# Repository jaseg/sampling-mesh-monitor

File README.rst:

High Fidelity Security Mesh Monitoring using Low-Cost, Embedded Time Domain Reflectometry
=========================================================================================

This repository contains all sources for our paper "High Fidelity Security Mesh Monitoring using Low-Cost, Embedded Time
Domain Reflectometry" to be published in CHES 2026/1 (`preprint on eprint <https://eprint.iacr.org/2025/1962>`__). You
can find a brief overview of the project `on Jan's blog <https://jaseg.de/blog/paper-sampling-mesh-monitor/>`__.

The canonical hosting location for this repo is https://git.jaseg.de/sampling-mesh-monitor.git . For comments or
questions, please reach out to Jan via `email <mailto:research@jaseg.de>`__ or `on mastodon
<https://chaos.social/@jaseg>`__.

.. figure:: paper/pic_board_setup_2_small.jpg
    :align: center
    :width: 400px
    :alt: A PCB with several chips sitting on a table with another PCB with only traces on it plugged in through a
          board-edge connector. The first PCB looks not very complex.

    The final setup. On the right is the measurement board, and on the left is the mesh test specimen plugged in. In a
    real application, you would integrate both into your target circuit.

Paper abstract
--------------

    Security Meshes are patterns of sensing traces covering an area that are used in Hardware Security Modules (HSMs)
    and other systems to detect attempts to physically intrude into the device's protective shell. State-of-the-art
    solutions manufacture meshes in bespoke processes from carefully chosen materials, which is expensive and makes
    replication challenging. Additionally, state-of-the-art monitoring circuits sacrifice either monitoring precision or
    cost efficiency. In this paper, we present an embeddable security mesh monitoring circuit constructed from low-cost,
    standard components that utilizes Time Domain Reflectometry (TDR) to create a unique fingerprint of a mesh. Our
    approach is both low-cost and precise, and enables the use of inexpensive standard Printed Circuit Boards (PCBs) as
    security mesh material. We demonstrate a working prototype of our TDR circuit costing less than 10 € in components
    that achieves both time resolution and rise time better than 200 ps—a 25 × improvement over previous work. We
    demonstrate a simple classifier that detects several types of advanced attacks such as probing using an oscilloscope
    probe or micro-soldering attacks with no false negatives.

Repo structure
--------------

``main_pcb``
    KiCad design files, exports and manufacturing files for the main circuit board. This board contains the measurement
    circuit, and has a connector for test coupons to be inserted. Data is read out throught the SWD interface using an
    SWD adapter. The board is a 6-layer PCB. The circuit is described in detail in the paper. It is based around a
    ``STM32G474RE`` ARM microcontroller.

``test_coupons``
    KiCad design files, exports and manufacturing files for the test coupon PCBs. The coupons are four-layer boards.
    Each coupon contains four test meshes, two on each side, that can be connected through four SFP form factor board
    edge connectors at the coupon's corners.

``firmware``
    Source code for the board firmware as well as tooling for running the experiments. The firmware is written in C, and
    you'll need a standard ARM GCC/binutils toolchain to build it. The experiment tool is a python script that connects
    to the board through GDB and exposes a local web server for controlling the board, monitoring the measurements in
    real time, and capturing data.

``analysis``
    All raw data, as well as the Jupyter notebooks used for analysis and plotting. By running these notebooks, you can
    re-run the analysis, and re-export all plots in the paper. The raw data is contained in JSON files, one per
    measurement series. Each JSON file contains some metadata describing the experiment and the settings used during the
    experiment, a set of calibration runs with the target specimen disconnected using the board's routing switches, and
    a full set of 12 measurement arrays consisting of a mean and standard deviation for each data point. To save space,
    batches of these JSON files are aggregated into zip archives. The analysis Jupyter notebooks will automatically load
    and decode the data from these zip archives when run.

``paper``
    The source of the accepted TCHES 2026-01 paper, as well as exports of all plots.

``talk``
    The presentation slides of the talk at CHES 2026 in Antalya, Türkiye.

Running the analysis
--------------------

To re-run the analysis, first install `Jupyter Lab <https://jupyter.org/>`__ and the `numpy <https://numpy.org/>`__ and
`scipy <https://scipy.org/>`__ python packages. If you're running in a virtualenv or on a weird platform like Windows or
MacOS, make sure that jupyter and pip agree where your python lives and the packages get installed in the right place.

Afterwards, just run ``jupyter lab`` in the ``analysis/jupyter_notebooks`` directory. You can then open any of the
notebooks through the left side panel and re-run the analysis within. Make sure you run all of the setup code at the top
of the notebook once before trying to run the analaysis code in the cells below. The analysis code only uses standard
scientific python packages that you probably already have installed. If you get an ``ImportError``, make sure the
packages listed in the file ``analysis/jupyter_notebooks/requirements.txt`` are installed.

The notebooks will display the plots and results inside Jupyter Lab and will also automatically export the plots to the
``paper`` directory of your clone of the git repository.

PCB Designs
-----------

This repo includes both the raw CAD files of the PCBs, as well as exported manufacturing data for easier viewing if you
don't have KiCad installed. The schematics are included as PDF exports.

The PCB designs were prepared in the open source KiCad_ EDA tool. Note that for some files you might need to download a
KiCad nightly build depending on how new your KiCad version is.

PCB design folder structure
...........................

``foobar.{kicad_pro,kicad_sch,kicad_pcb,etc.}``
    The KiCad source files of the PCB. Open the ``.kicad_pro`` file in KiCad, then you can open the schematics and board
    layout from there.

``fab/gerbers.zip``
    Gerber exports of the board layouts. You can open these in any Gerber viewer such as gerbv_. These files are
    essentially vector graphics exports of the board layout. They show what copper, silkscreen etc. you see on the
    board, but they don't include any semantic information such as component values. You can send this zip directly to a
    PCB manufacturer and they will be able to manufacture these boards for you. The order parameters are included in the
    gerber files on the ``User.Comments`` layer.

``fab/{bom.csv,pos.csv}``
    Bill of materials and component placement coordinate files for board manufacturing. If you want a contract
    manufacturer to solder these boards for you, you need to give them these two files in addition to the gerbers. The
    BOM tells them what exact parts and how many of them you need, the position file tells them where to put them on the
    board. We had JLCPCB make the PCBs, and we also had them solder most of the parts. Some parts we soldered after the
    fact by hand because JLC didn't have them in stock, and getting them to order and solder them for us would have been
    pretty expensive.

    If you want to solder the main PCB yourself, you need some prior experience in fine SMD work and a decently setup
    electronics lab with a microscope, a hot air reworks station, etc.

    Note: **The PCB revision here does not have a functional driver IC!** For our lab experiments we microsoldered
    the four different driver ICs by hand to avoid having to spin multiple copies of this expensive PCB. For some basic
    measurements, you can just omit the driver IC included in the design and bridge it. This will drive the mesh
    directly from the ``74LVC2G157`` gates, which is enough for some basic measurements.

``schematics/*.pdf``
    PDF export of the schematics of the board.

Firmware
--------

The firmware and associated scripts are contained in the ``firmware`` directory.

Building the firmware
.....................

If you have an ARM GCC toolchain installed, you can build the firmware by running ``make`` in this directory. During
build, the makefile exports some diagnostic information about the build artifacts. For that to work, you have to have
the `cxxfilt python package <https://pypi.org/project/cxxfilt/>`__ installed. If the package can't be found, the
firmware will still be built, but you will get a crash in the makefile during the analysis step that runs after the
build was successful.

Running experiments
...................

To run an experiment, you need a measurement board and a test coupon. You also need the following software installed on
your machine:

* ``openocd``
* ``arm-none-eabi-gdb`` (another ABI arm gdb should work too)
* The python packages listed in ``firmware/requirements.txt``

To build the firmware, you additionally need a ARM toolchain installed. By default, the makefile assumes gcc/gnu
binutils, but you can override that if you prefer to use LLVM.

To run an experiment, connect the board to power via USB, and to your computer through an SWD debug adapter. We used
cheap STLinkV2 clones, if you have a different adapter you'll have to modify the ``.gdbinit`` script accordingly. After
connecting the board, open three terminal windows running the following three commands one per window, in this order.

1. ``openocd -f openocd.cfg``
2. ``arm-none-eabi-gdb build/main.elf``
3. ``python adc_serve.py``

This will connect to the board and start the realtime control and measurement web interface. You can open the web
interface at the location printed by ``adc_serve.py`` on startup.

If you're cheap like us and use a STLinkV2 clone SWD adapter, it may be that openocd takes a few (maybe up to five or
so) attempts to start up and connect to the microcontroller. After starting, the GDB terminal should start printing a
few lines of output every 30 seconds or so when it saves a measurement series. If GDB starts to hang, it might be that
you bumped a cable or accidentially shorted something on the board. To re-start, you first kill gdb (Ctrl+C, then
Ctrl+D, then Ctrl+D again), then you stop openocd (Ctrl+C, kill it if it doesn't stop in a few seconds), then you
restart them in the order above. You don't have to restart the web interface, just adjust any of the knobs to overwrite
the default control settings again.

Firmware Folder Structure
.........................

``src/main.c``
    The source code of the mainboard firmware. This firmware captures data into internal buffers, which are read out
    from the host through SWD.

``openocd.cfg``
    OpenOCD script for connecting to the debug adapter. We used cheap STLinkV2 clones from aliexpress. If you use a
    different debug adapter, you will have to modify this file accordingly to tell OpenOCD how to connect to the board.
    The port numbers given here and in the ``.gdbinit`` must match up.

``.gdbinit``
    GDB script running the data extraction. This script will continuously dump the measurement data into ``/tmp`` every
    time a measurement series has been completed. Note that this file will be hidden on unixes. Also note that you will
    have to explicitly allowlist this file's absolute path on your computer in your ``$HOME/.gdbinit`` the first time
    you run it because gdb refuses to run unknown ``.gdbinit`` files for security.

``adc_serve.py``
    Real-time monitoring and data capture tool. Before running this, first make sure you have gdb attached to the board
    using the ``.gdbinit``. The tool communicates with the gdb script through files in ``/tmp``. It exposes a web
    interface that displays the captured data in real time, allows you to change the board's measurement settings, and
    allows you to export measurement series.

``make_barcodes.py``
    This is a helper script we used to create barcode labels for all ~120 test specimens to simplify the measurement
    workflow. We had a barcode reader hooked up to the computer running the measurements, so you could just scan a
    specimen's barcode to capture a data series registered to that board in the web interface.
    
other files:
    Build files for the firmware. These are mostly generic to this type of microcontroller and are included here so the
    firmware source is self-contained.

.. _KiCad: https://www.kicad.org/
.. _gerbv: https://gerbv.github.io/

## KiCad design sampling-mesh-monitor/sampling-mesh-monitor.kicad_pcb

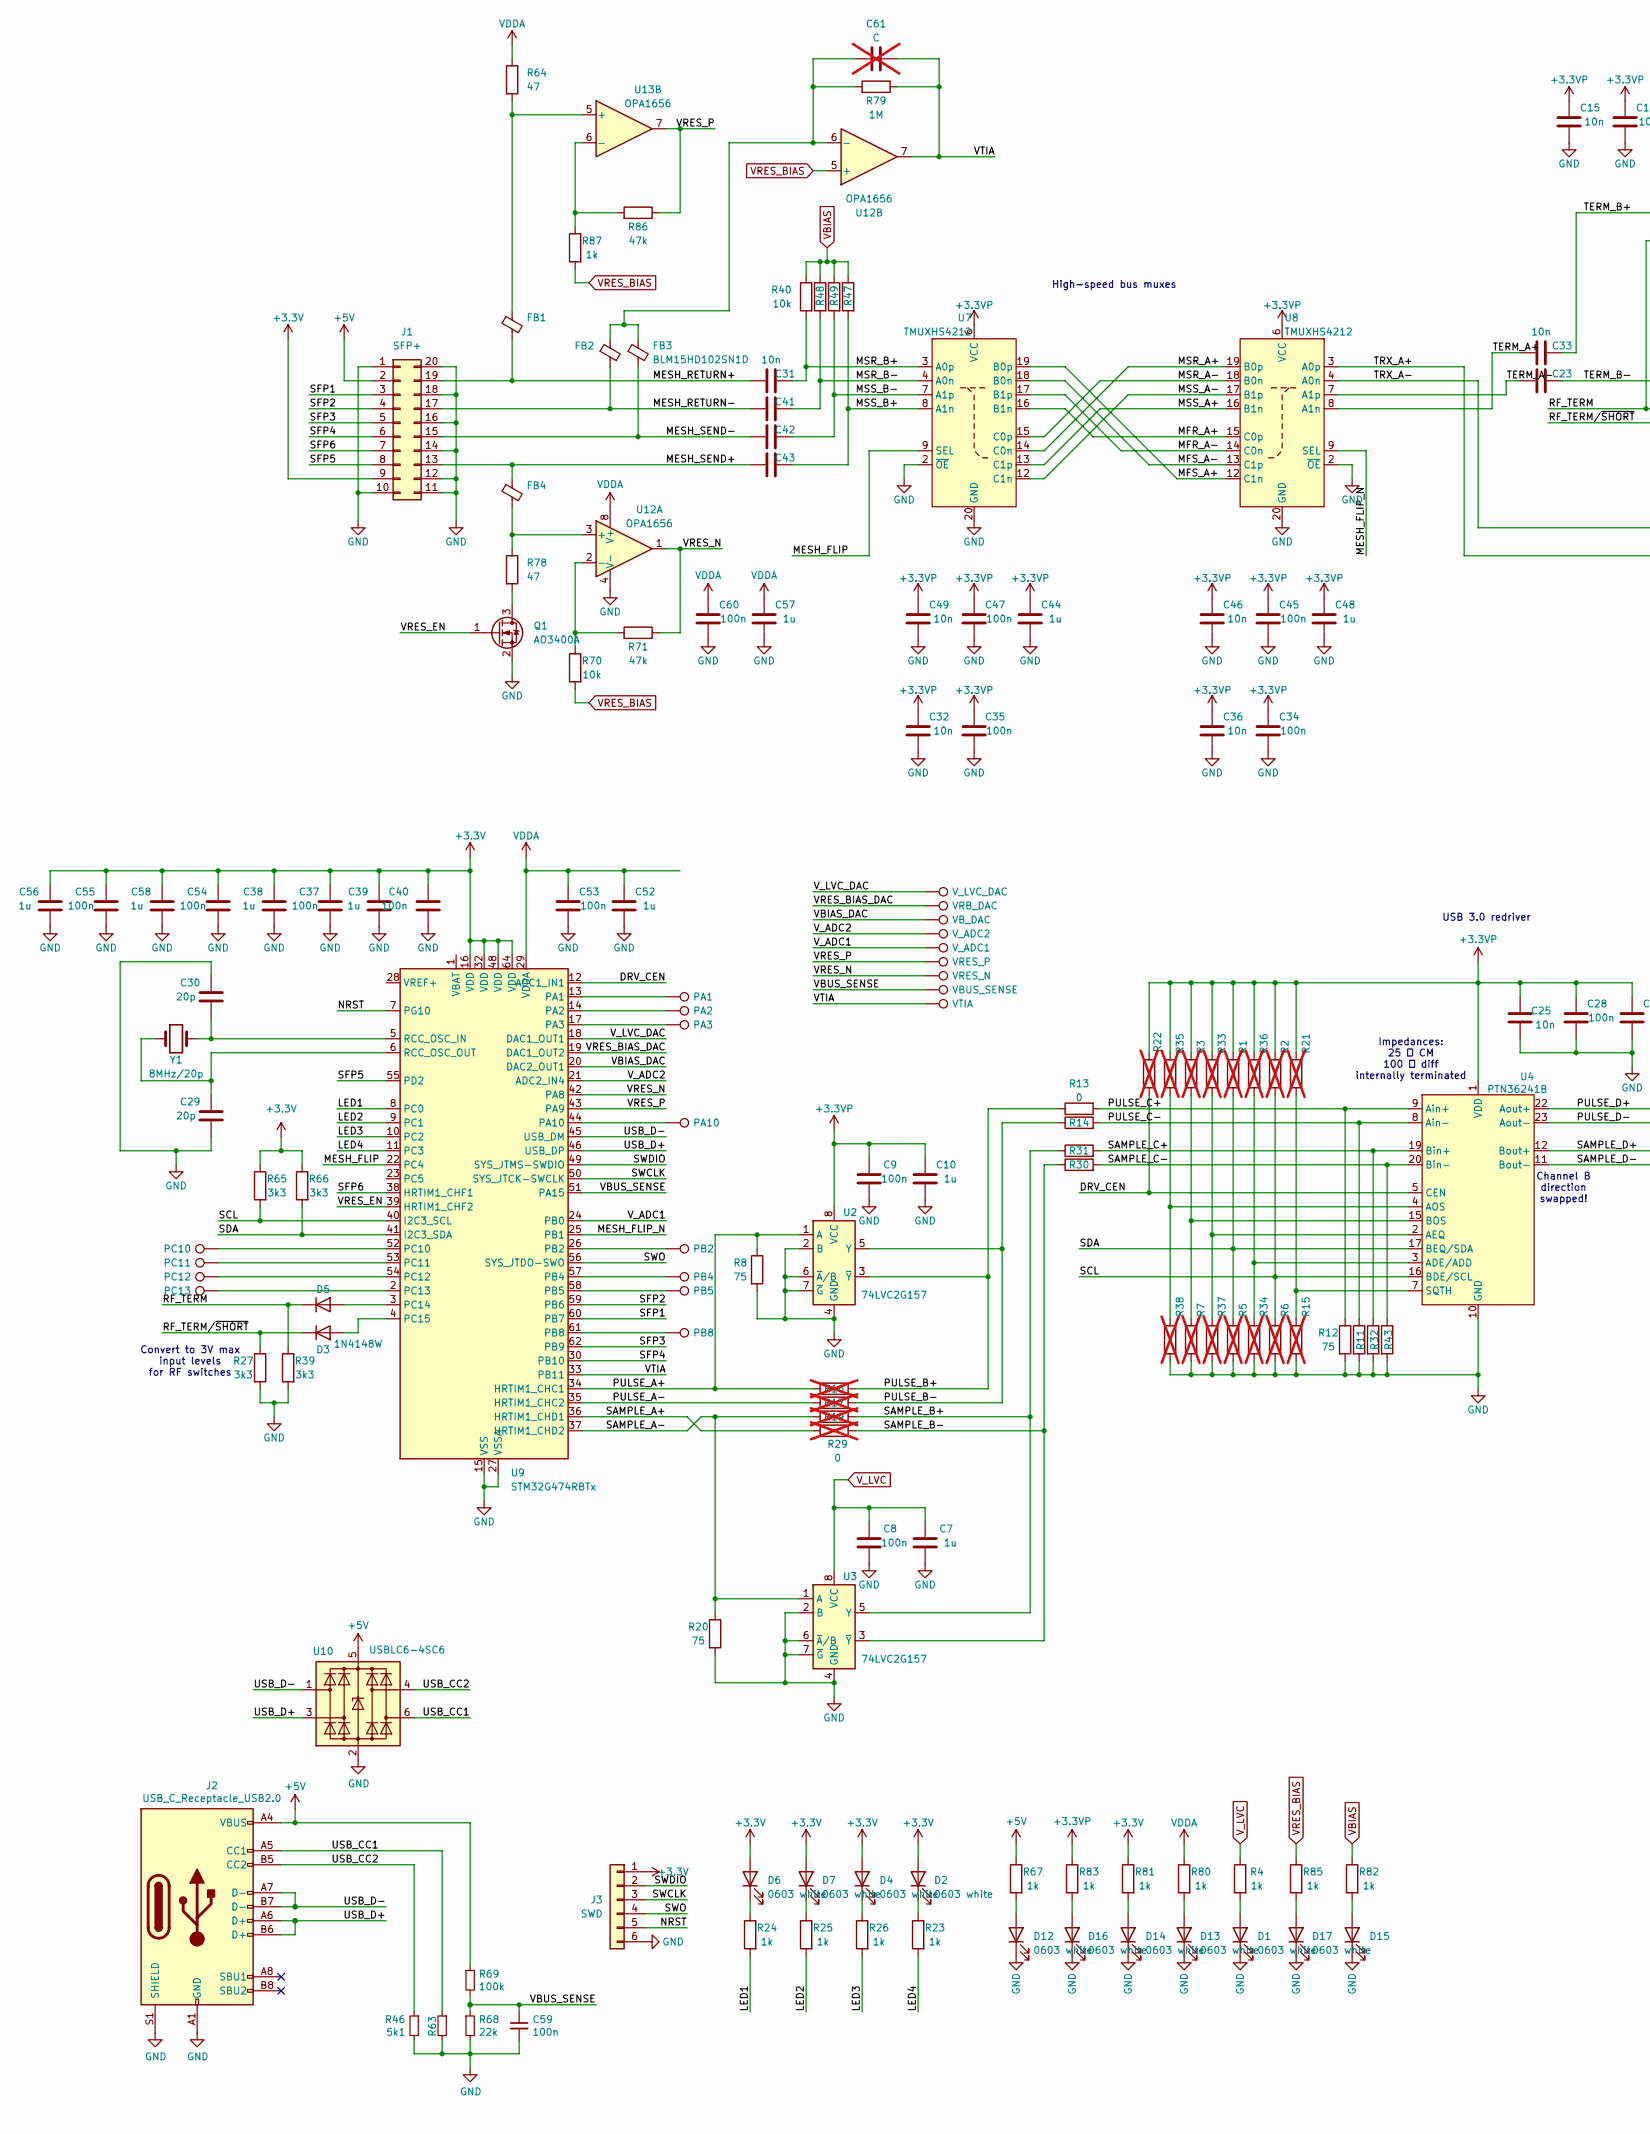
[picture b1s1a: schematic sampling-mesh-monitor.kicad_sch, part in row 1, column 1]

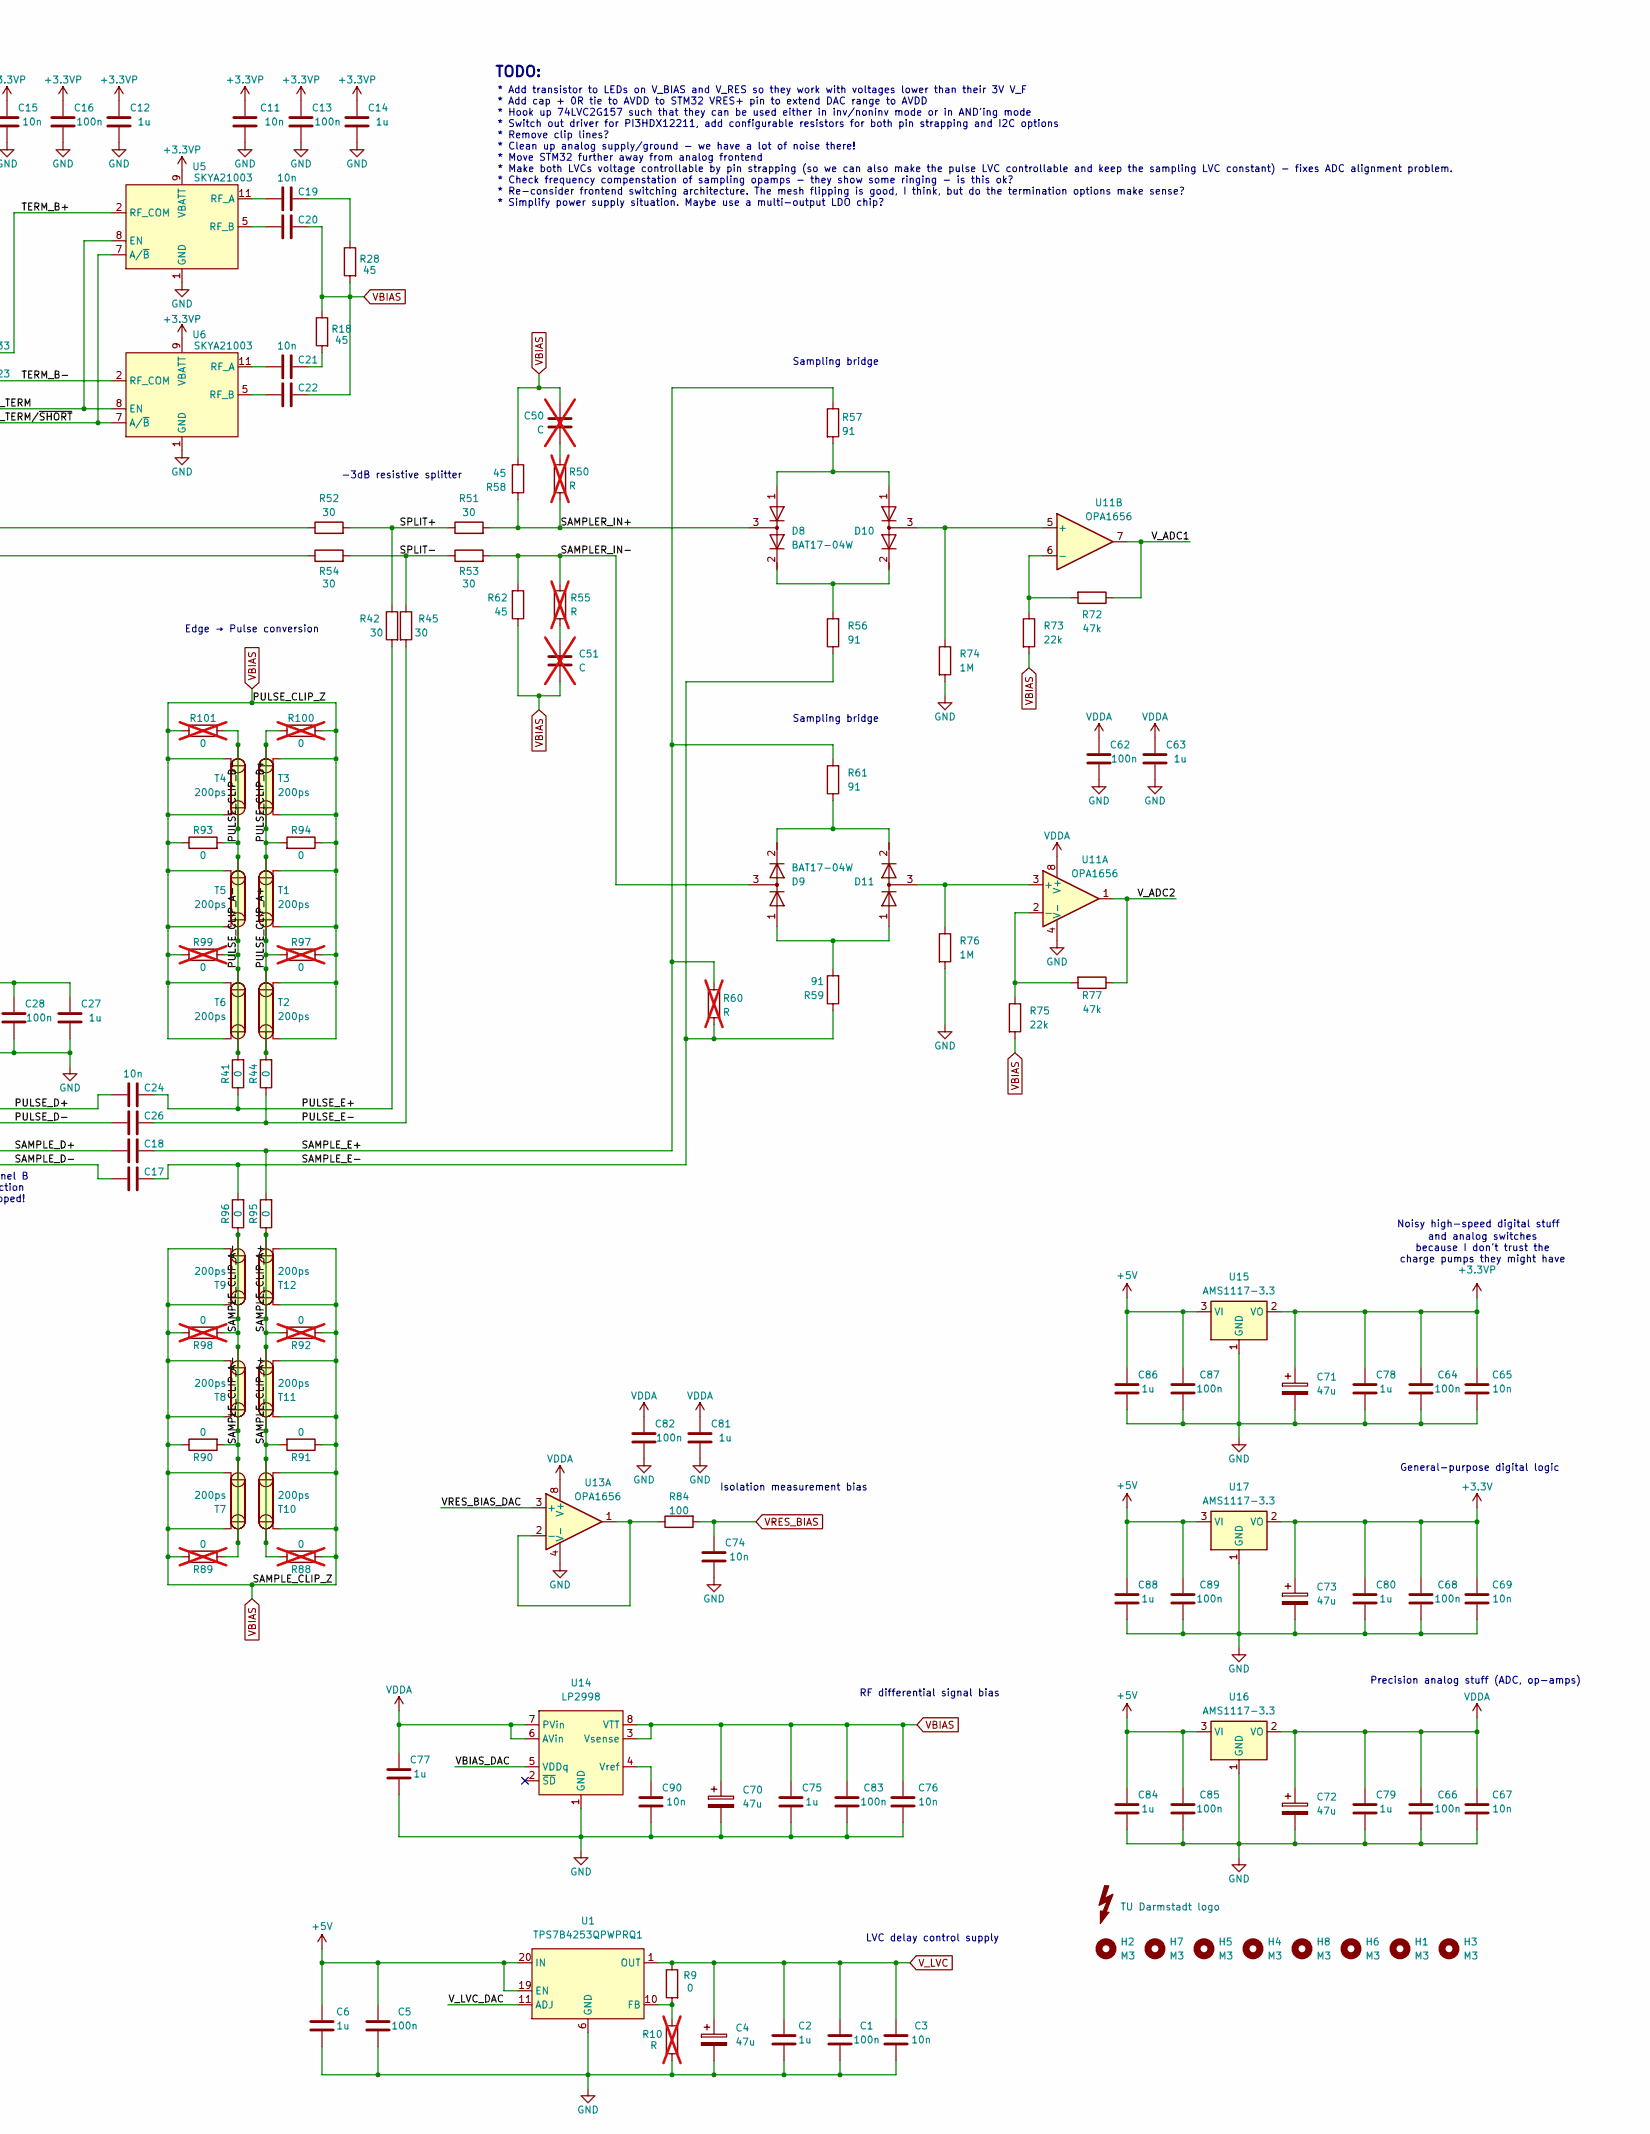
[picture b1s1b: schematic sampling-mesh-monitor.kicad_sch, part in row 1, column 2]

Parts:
C1, C5, C8, C9, C13, C16, C28, C34, C35, C37, C40, C45, C47, C53, C54, C55, C59, C60, C62, C64, C66, C68, C82, C83, C85, C87, C89: 100n; C_0402_1005Metric; LCSC C307331
C2, C6, C7, C10, C12, C14, C27, C38, C39, C44, C48, C52, C56, C57, C58, C63, C75, C77, C78, C79, C80, C81, C84, C86, C88: 1u; C_0805_2012Metric; LCSC C28323
C3, C11, C15, C17, C18, C19, C20, C21, C22, C23, C24, C25, C26, C31, C32, C33, C36, C41, C42, C43, C46, C49, C65, C67, C69, C74, C76, C90: 10n; C_0402_1005Metric; LCSC C15195
C4, C70, C71, C72, C73: 47u; C_Elec_6.3x7.7; LCSC C88810
C29, C30: 20p; C_0402_1005Metric; LCSC C1554
C50, C51, C61: C; C_0402_1005Metric; not fitted
D1, D2, D4, D6, D7, D12, D13, D14, D15, D16, D17: 0603 white; LED_0603_1608Metric; LCSC C2290
D3, D5: 1N4148W; D_SOD-123; LCSC C81598
D8, D9, D10, D11: BAT17-04W; SOT-323_SC-70; LCSC C503474
FB1, FB2, FB3, FB4: BLM15HD102SN1D; L_0402_1005Metric; LCSC C21516
GR1: TU Darmstadt logo; logo_tu_darmstadt_25.0mm
H1, H2, H3, H4, H5, H6, H7, H8: M3; MountingHole_3.2mm_M3_DIN965
J1: SFP+; HCTL_HC-SFP-20P_C2897291; LCSC C2897291
J2: USB_C_Receptacle_USB2.0; USB_C_Receptacle_HCTL_HC-TYPE-C-16P-01A; LCSC C2988369
J3: SWD; Würth_WR-WST_debug_490107670612_2x03_P2.54mm_Vertical
Q1: AO3400A; SOT-23; LCSC C20917
R1, R2, R3, R5, R6, R7, R10, R15, R21, R22, R33, R34, R35, R36, R37, R38, R50, R55, R60: R; R_0402_1005Metric; not fitted
R4, R23, R24, R25, R26, R67, R80, R81, R82, R83, R85, R87: 1k; R_0402_1005Metric; LCSC C11702
R8, R11, R12, R20, R32, R43: 75; R_0402_1005Metric; LCSC C25133
R9, R13, R14, R30, R31, R41, R44, R90, R91, R93, R94, R95, R96: 0; R_0402_1005Metric; LCSC C17168
R16, R17, R19, R29, R88, R89, R92, R97, R98, R99, R100, R101: 0; R_0402_1005Metric; LCSC C17168; not fitted
R18, R28, R58, R62: 45; R_0402_1005Metric; LCSC C327342
R27, R39, R65, R66: 3k3; R_0402_1005Metric; LCSC C25890
R40, R47, R48, R49, R70: 10k; R_0402_1005Metric; LCSC C2654005
R42, R45, R51, R52, R53, R54: 30; R_0402_1005Metric; LCSC C138007
R46, R63: 5k1; R_0402_1005Metric; LCSC C25905
R56, R57, R59, R61: 91; R_0402_1005Metric; LCSC C4071412
R64, R78: 47; R_0603_1608Metric; LCSC C23182
R68, R73, R75: 22k; R_0402_1005Metric; LCSC C25768
R69: 100k; R_0402_1005Metric; LCSC C25741
R71, R72, R77, R86: 47k; R_0402_1005Metric; LCSC C25792
R74, R76, R79: 1M; R_0402_1005Metric; LCSC C138033
R84: 100; R_0402_1005Metric; LCSC C25076
T1, T2, T3, T4, T5, T6, T7, T8, T9, T10, T11, T12: 200ps
TP1: V_LVC_DAC; TestPoint_Pad_1.5x1.5mm
TP2: PA2; TestPoint_Pad_1.5x1.5mm
TP3: PA1; TestPoint_Pad_1.5x1.5mm
TP4: PC13; TestPoint_Pad_1.5x1.5mm
TP5: VRB_DAC; TestPoint_Pad_1.5x1.5mm
TP6: PA3; TestPoint_Pad_1.5x1.5mm
TP7: PB2; TestPoint_Pad_1.5x1.5mm
TP8: PB5; TestPoint_Pad_1.5x1.5mm
TP9: PB8; TestPoint_Pad_1.5x1.5mm
TP10: PC12; TestPoint_Pad_1.5x1.5mm
TP11: PB4; TestPoint_Pad_1.5x1.5mm
TP12: PC11; TestPoint_Pad_1.5x1.5mm
TP13: PC10; TestPoint_Pad_1.5x1.5mm
TP14: PA10; TestPoint_Pad_1.5x1.5mm
TP15: VBUS_SENSE; TestPoint_Pad_1.5x1.5mm
TP16: VRES_N; TestPoint_Pad_1.5x1.5mm
TP17: VTIA; TestPoint_Pad_1.5x1.5mm
TP18: V_ADC1; TestPoint_Pad_1.5x1.5mm
TP19: V_ADC2; TestPoint_Pad_1.5x1.5mm
TP20: VRES_P; TestPoint_Pad_1.5x1.5mm
TP21: VB_DAC; TestPoint_Pad_1.5x1.5mm
U1: TPS7B4253QPWPRQ1; HTSSOP-20-1EP_4.4x6.5mm_P0.65mm_EP3.4x6.5mm_Mask2.4x3.7mm; LCSC C2879376
U2, U3: 74LVC2G157; MSOP-8_3x3mm_P0.65mm; LCSC C78048
U4: PTN36241B; QFN-24-1EP_4x4mm_P0.5mm_EP2.6x2.6mm; LCSC C2675242
U5, U6: SKYA21003; QFN-12_EP_2x2_Pitch0.5mm; LCSC C141440
U7, U8: TMUXHS4212; DHVQFN-20-1EP_2.5x4.5mm_P0.5mm_EP1x3mm; LCSC C3656912
U9: STM32G474RBTx; LQFP-64_10x10mm_P0.5mm; LCSC C529413
U10: USBLC6-4SC6; SOT-23-6; LCSC C558419
U11, U12, U13: OPA1656; SO-8_3.9x4.9mm_P1.27mm; LCSC C1849431
U14: LP2998; SOIC-8-1EP_3.9x4.9mm_P1.27mm_EP2.34x2.34mm; LCSC C181400
U15, U16, U17: AMS1117-3.3; SOT-223-3_TabPin2; LCSC C6186
Y1: 8MHz/20p; Crystal_SMD_5032-2Pin_5.0x3.2mm; LCSC C115962

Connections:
+3.3V: C37.2, C38.2, C39.2, C40.2, C54.2, C55.2, C56.2, C58.2, C68.2, C69.2, C73.1, C80.2, D2.2 (A), D4.2 (A), D6.2 (A), D7.2 (A), J1.9, J3.1, R65.1, R66.1, R81.1, U9.16 (VDD), U9.32 (VDD), U9.48 (VDD), U9.64 (VDD), U17.2 (VO)
+3.3VP: C9.2, C10.2, C11.2, C12.2, C13.2, C14.2, C15.2, C16.2, C25.2, C27.2, C28.2, C32.2, C34.2, C35.2, C36.2, C44.2, C45.2, C46.2, C47.2, C48.2, C49.2, C64.2, C65.2, C71.1, C78.2, R1.1, R2.1, R3.1, R21.1, R22.1, R33.1, R35.1, R36.1, R83.1, U2.8 (VCC), U4.1 (VDD), U4.13 (VDD), U5.9 (VBATT), U6.9 (VBATT), U7.1 (RSVD1), U7.6 (VCC), U7.10 (RSVD2), U8.1 (RSVD1), U8.6 (VCC), U8.10 (RSVD2), U15.2 (VO)
+5V: C5.2, C6.2, C84.2, C85.2, C86.2, C87.2, C88.2, C89.2, J1.2, J2.A4 (VBUS), J2.A9 (VBUS), J2.B4 (VBUS), J2.B9 (VBUS), R67.1, R69.1, U1.19 (EN), U1.20 (IN), U10.5 (VBUS), U15.3 (VI), U16.3 (VI), U17.3 (VI)
/DRV_CEN: R22.2, U4.5 (CEN), U9.12 (ADC1_IN1)
/LED1: R24.2, U9.8 (PC0)
/LED2: R25.2, U9.9 (PC1)
/LED3: R26.2, U9.10 (PC2)
/LED4: R23.2, U9.11 (PC3)
/MESH_FLIP: U7.9 (SEL), U9.22 (PC4)
/MESH_FLIP_N: U8.9 (SEL), U9.25 (PB1)
/MESH_RETURN+: C31.1, FB1.2, J1.19
/MESH_RETURN-: C41.1, FB2.2, J1.17
/MESH_SEND+: C43.1, FB4.1, J1.13
/MESH_SEND-: C42.1, FB3.2, J1.15
/MFR_A+: U7.16 (B1n), U8.15 (C0p)
/MFR_A-: U7.17 (B1p), U8.14 (C0n)
/MFS_A+: U7.19 (B0p), U8.12 (C1n)
/MFS_A-: U7.18 (B0n), U8.13 (C1p)
/MSR_A+: U7.14 (C0n), U8.19 (B0p)
/MSR_A-: U7.15 (C0p), U8.18 (B0n)
/MSR_B+: C31.2, R40.2, U7.3 (A0p)
/MSR_B-: C41.2, R48.2, U7.4 (A0n)
/MSS_A+: U7.13 (C1p), U8.16 (B1n)
/MSS_A-: U7.12 (C1n), U8.17 (B1p)
/MSS_B+: C43.2, R47.2, U7.8 (A1n)
/MSS_B-: C42.2, R49.2, U7.7 (A1p)
/NRST: J3.5, U9.7 (PG10)
/PULSE_A+: R8.1, R16.1, U2.1 (A), U9.34 (HRTIM1_CHC1)
/PULSE_A-: R17.1, U9.35 (HRTIM1_CHC2)
/PULSE_B+: R13.1, R16.2, U2.3 (~Y)
/PULSE_B-: R14.1, R17.2, U2.5 (Y)
/PULSE_C+: R12.1, R13.2, U4.9 (Ain+)
/PULSE_C-: R11.1, R14.2, U4.8 (Ain-)
/PULSE_CLIP_A+: R44.2, R94.2, R97.2, R100.2, T1.1, T1.3, T2.1, T2.3, T3.1, T3.3
/PULSE_CLIP_A-: R41.2, R93.2, R99.2, R101.2, T4.1, T4.3, T5.1, T5.3, T6.1, T6.3
/PULSE_D+: C24.2, U4.22 (Aout+)
/PULSE_D-: C26.2, U4.23 (Aout-)
/PULSE_E+: C24.1, R41.1, R42.2
/PULSE_E-: C26.1, R44.1, R45.2
/RF_TERM: D5.1 (K), R39.1, U5.8 (EN), U6.8 (EN)
/RF_TERM/~SHORT: D3.1 (K), R27.1, U5.7 (A/~B), U6.7 (A/~B)
/SAMPLER_IN+: D8.3 (common), R50.2, R51.2, R58.2
/SAMPLER_IN-: D9.3 (common), R53.2, R55.2, R62.2
/SAMPLE_A+: R29.1, U9.36 (HRTIM1_CHD1)
/SAMPLE_A-: R19.1, R20.1, U3.1 (A), U9.37 (HRTIM1_CHD2)
/SAMPLE_B+: R19.2, R31.1, U3.5 (Y)
/SAMPLE_B-: R29.2, R30.1, U3.3 (~Y)
/SAMPLE_C+: R31.2, R32.1, U4.19 (Bin+)
/SAMPLE_C-: R30.2, R43.1, U4.20 (Bin-)
/SAMPLE_CLIP_A+: R88.2, R91.2, R92.2, R95.1, T10.1, T10.3, T11.1, T11.3, T12.1, T12.3
/SAMPLE_CLIP_A-: R89.2, R90.2, R96.1, R98.2, T7.1, T7.3, T8.1, T8.3, T9.1, T9.3
/SAMPLE_D+: C18.2, U4.12 (Bout+)
/SAMPLE_D-: C17.2, U4.11 (Bout-)
/SAMPLE_E+: C18.1, R57.1, R60.1, R61.2, R95.2
/SAMPLE_E-: C17.1, R56.1, R59.1, R60.2, R96.2
/SCL: R2.2, R6.1, R65.2, U4.16 (BDE/SCL), U9.40 (I2C3_SCL)
/SDA: R1.2, R5.1, R66.2, U4.17 (BEQ/SDA), U9.41 (I2C3_SDA)
/SFP1: J1.3, U9.60 (PB7)
/SFP2: J1.4, U9.59 (PB6)
/SFP3: J1.5, U9.62 (PB9)
/SFP4: J1.6, U9.30 (PB10)
/SFP5: J1.8, U9.55 (PD2)
/SFP6: J1.7, U9.38 (HRTIM1_CHF1)
/SPLIT+: R42.1, R51.1, R52.2
/SPLIT-: R45.1, R53.1, R54.2
/SWCLK: J3.3, U9.50 (SYS_JTCK-SWCLK)
/SWDIO: J3.2, U9.49 (SYS_JTMS-SWDIO)
/SWO: J3.4, U9.56 (SYS_JTDO-SWO)
/TERM_A+: C33.2, U8.8 (A1n)
/TERM_A-: C23.2, U8.7 (A1p)
/TERM_B+: C33.1, U5.2 (RF_COM)
/TRX_A+: R54.1, U8.3 (A0p)
/TRX_A-: R52.1, U8.4 (A0n)
/USB_CC1: J2.A5 (CC1), R63.1, U10.6 (I/O4)
/USB_CC2: J2.B5 (CC2), R46.1, U10.4 (I/O3)
/USB_D+: J2.A6 (D+), J2.B6 (D+), U9.46 (USB_DP), U10.3 (I/O2)
/USB_D-: J2.A7 (D-), J2.B7 (D-), U9.45 (USB_DM), U10.1 (I/O1)
/VBIAS_DAC: TP21.1, U9.20 (DAC2_OUT1), U14.5 (VDDq)
/VBUS_SENSE: C59.1, R68.1, R69.2, TP15.1, U9.51 (PA15)
/VRES_BIAS_DAC: TP5.1, U9.19 (DAC1_OUT2), U13.3 (+)
/VRES_EN: Q1.1 (G), U9.39 (HRTIM1_CHF2)
/VRES_N: R71.1, TP16.1, U9.42 (PA8), U12.1
/VRES_P: R86.1, TP20.1, U9.43 (PA9), U13.7
/VTIA: C61.2, R79.1, TP17.1, U9.33 (PB11), U12.7
/V_ADC1: R72.1, TP18.1, U9.24 (PB0), U11.7
/V_ADC2: R77.1, TP19.1, U9.21 (ADC2_IN4), U11.1
/V_LVC_DAC: TP1.1, U1.11 (ADJ), U9.18 (DAC1_OUT1)
GND: C1.1, C2.1, C3.1, C4.2, C5.1, C6.1, C7.1, C8.1, C9.1, C10.1, C11.1, C12.1, C13.1, C14.1, C15.1, C16.1, C25.1, C27.1, C28.1, C29.1, C30.2, C32.1, C34.1, C35.1, C36.1, C37.1, C38.1, C39.1, C40.1, C44.1, C45.1, C46.1, C47.1, C48.1, C49.1, C52.1, C53.1, C54.1, C55.1, C56.1, C57.1, C58.1, C59.2, C60.1, C62.1, C63.1, C64.1, C65.1, C66.1, C67.1, C68.1, C69.1, C70.2, C71.2, C72.2, C73.2, C74.1, C75.1, C76.1, C77.1, C78.1, C79.1, C80.1, C81.1, C82.1, C83.1, C84.1, C85.1, C86.1, C87.1, C88.1, C89.1, C90.1, D1.1 (K), D12.1 (K), D13.1 (K), D14.1 (K), D15.1 (K), D16.1 (K), D17.1 (K), J1.1, J1.10, J1.11, J1.12, J1.14, J1.16, J1.18, J1.20, J2.A1 (GND), J2.A12 (GND), J2.B1 (GND), J2.B12 (GND), J2.S1 (SHIELD), J3.6, Q1.2 (S), R5.2, R6.2, R7.2, R8.2, R10.2, R11.2, R12.2, R15.2, R20.2, R27.2, R32.2, R34.2, R37.2, R38.2, R39.2, R43.2, R46.2, R63.2, R68.2, R74.2, R76.2, U1.6 (GND), U1.15 (GND), U1.21 (GND), U2.2 (B), U2.4 (GND), U2.6 (~A/B), U2.7 (~G), U3.2 (B), U3.4 (GND), U3.6 (~A/B), U3.7 (~G), U4.6 (GND), U4.10 (GND), U4.14 (RES), U4.18 (GND), U4.21 (GND), U4.25 (GND), U5.1 (GND), U5.3 (GND), U5.4 (GND), U5.6 (GND), U5.10 (GND), U5.12 (GND), U5.13 (GND), U6.1 (GND), U6.3 (GND), U6.4 (GND), U6.6 (GND), U6.10 (GND), U6.12 (GND), U6.13 (GND), U7.2 (~OE), U7.5 (GND), U7.11 (GND), U7.20 (GND), U7.21 (GND), U8.2 (~OE), U8.5 (GND), U8.11 (GND), U8.20 (GND), U8.21 (GND), U9.15 (VSS), U9.27 (VSSA), U9.31 (VSS), U9.47 (VSS), U9.63 (VSS), U10.2 (GND), U11.4 (V-), U12.4 (V-), U13.4 (V-), U14.1 (GND), U14.9 (GND), U15.1 (GND), U16.1 (GND), U17.1 (GND)
unnamed: C50.2, R50.1
unnamed: C19.1, R28.1
unnamed: C21.1, R18.2
unnamed: C51.1, R55.1
unnamed: D8.1 (A), D10.1 (A), R57.2
unnamed: D8.2 (K), D10.2 (K), R56.2
unnamed: D10.3 (common), R74.1, U11.5 (+)
unnamed: D9.1 (A), D11.1 (A), R59.2
unnamed: D9.2 (K), D11.2 (K), R61.1
unnamed: D11.3 (common), R76.1, U11.3 (+)
unnamed: D5.2 (A), U9.3 (PC14)
unnamed: D3.2 (A), U9.4 (PC15)
unnamed: D7.1 (K), R25.1
unnamed: D6.1 (K), R24.1
unnamed: D4.1 (K), R26.1
unnamed: D2.1 (K), R23.1
unnamed: D12.2 (A), R67.2
unnamed: D16.2 (A), R83.2
unnamed: D14.2 (A), R81.2
unnamed: D13.2 (A), R80.2
unnamed: D1.2 (A), R4.2
unnamed: D17.2 (A), R85.2
unnamed: D15.2 (A), R82.2
unnamed: Q1.3 (D), R78.2
unnamed: FB4.2, R78.1, U12.3 (+)
unnamed: R70.1, R71.2, U12.2 (-)
unnamed: C61.1, FB2.1, FB3.1, R79.2, U12.6 (-)
unnamed: R84.1, U13.1, U13.2 (-)
unnamed: FB1.1, R64.2, U13.5 (+)
unnamed: R86.2, R87.1, U13.6 (-)
unnamed: C90.2, U14.4 (Vref)
unnamed: R34.1, R36.2, U4.3 (ADE/ADD)
unnamed: R33.2, R37.1, U4.2 (AEQ)
unnamed: R35.2, R38.1, U4.4 (AOS)
unnamed: R3.2, R7.1, U4.15 (BOS)
unnamed: R15.1, R21.2, U4.7 (SQTH)
unnamed: TP3.1, U9.13 (PA1)
unnamed: TP2.1, U9.14 (PA2)
unnamed: TP6.1, U9.17 (PA3)
unnamed: TP14.1, U9.44 (PA10)
unnamed: TP7.1, U9.26 (PB2)
unnamed: TP11.1, U9.57 (PB4)
unnamed: TP8.1, U9.58 (PB5)
unnamed: TP9.1, U9.61 (PB8)
unnamed: TP13.1, U9.52 (PC10)
unnamed: TP12.1, U9.53 (PC11)
unnamed: TP10.1, U9.54 (PC12)
unnamed: TP4.1, U9.2 (PC13)
unnamed: C30.1, U9.5 (RCC_OSC_IN), Y1.2
unnamed: C29.2, U9.6 (RCC_OSC_OUT), Y1.1
unnamed: C19.2, U5.11 (RF_A)
unnamed: C20.2, U5.5 (RF_B)
unnamed: C21.2, U6.11 (RF_A)
unnamed: C22.2, U6.5 (RF_B)
unnamed: C23.1, U6.2 (RF_COM)
unnamed: R75.1, R77.2, U11.2 (-)
unnamed: R72.2, R73.1, U11.6 (-)
unnamed: R9.2, R10.1, U1.10 (FB)
VBIAS: C20.1, C22.1, C50.1, C51.2, C70.1, C75.2, C76.2, C83.2, R18.1, R28.2, R40.1, R47.1, R48.1, R49.1, R58.1, R62.1, R73.2, R75.2, R82.1, R88.1, R89.1, R90.1, R91.1, R92.1, R93.1, R94.1, R97.1, R98.1, R99.1, R100.1, R101.1, T1.2, T1.4, T2.2, T2.4, T3.2, T3.4, T4.2, T4.4, T5.2, T5.4, T6.2, T6.4, T7.2, T7.4, T8.2, T8.4, T9.2, T9.4, T10.2, T10.4, T11.2, T11.4, T12.2, T12.4, U14.3 (Vsense), U14.8 (VTT)
VDDA: C52.2, C53.2, C57.2, C60.2, C62.2, C63.2, C66.2, C67.2, C72.1, C77.2, C79.2, C81.2, C82.2, R64.1, R80.1, U9.29 (VDDA), U11.8 (V+), U12.8 (V+), U13.8 (V+), U14.6 (AVin), U14.7 (PVin), U16.2 (VO)
VRES_BIAS: C74.2, R70.2, R84.2, R85.1, R87.2, U12.5 (+)
V_LVC: C1.2, C2.2, C3.2, C4.1, C7.2, C8.2, R4.1, R9.1, U1.1 (OUT), U3.8 (VCC)

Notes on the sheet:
General-purpose digital logic
and analog switches because I don't trust the charge pumps they might have
-3dB resistive splitter
Isolation measurement bias
Edge → Pulse conversion
Sampling bridge
USB 3.0 redriver
Channel B direction swapped!
RF differential signal bias
High-speed bus muxes
* Add transistor to LEDs on V_BIAS and V_RES so they work with voltages lower than their 3V V_F * Add cap + 0R tie to AVDD to STM32 VRES+ pin to extend DAC range to AVDD * Hook up 74LVC2G157 such that they can be used either in inv/noninv mode or in AND'ing mode * Switch out driver for PI3HDX12211,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
Precision analog stuff (ADC, op-amps)
LVC delay control supply
Noisy high-speed digital stuff
TODO:
Convert to 3V max input levels for RF switches
Impedances: 25  CM 100  diff internally terminated
